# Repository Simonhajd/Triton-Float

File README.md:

# Triton Float

Development repository for the 2026 Triton Robotics Float.

## Overview

The Triton Float is being developed for the 2026 MATE ROV Pioneer competition (Newfoundland).
This design iteration is approximately 33% smaller than last year's model, while targeting more than 2× performance improvements in speed and significantly increased precision through layered redundancy and sensor feedback systems. It also includes a dedicated LoRa radio as opposed to last year's 4cm wire antenna, which will increase the reliability and robustness of the system.

## Features

Dimensions: 200mm x 4 in diameter.
Buoyancy system: PWM pump ranging from 220mL/min to -220mL/min.

Accuracy Strategy:

- Internal pressure sensor for ballast state verification  
- Pump movement feedback sensor for closed-loop control  
- Pre-calibrated pump flow rate modeling for predictive adjustment
- Additional onboard MCU sensors for reproducible control accuracy

## Hardware / Electrical

- Microcontroller: XIAO nRF52840 Sense  

- Sensors:  
  - XIAO nRF52840 Sense onboard IMU & sensors  
  - Blue Robotics Bar02  
  - Internal pressure sensor  
  - Pump movement sensor  

- Power System:  
  Custom voltage regulation system controlled via relay and magnetic hall-effect sensor on a secondary accessory PCB  

- PCB Revisions:  
  R2 completed, R3 in development

## Mechanical Design

Fusion / CAD link:
🔗 [View Fusion 360 CAD](https://a360.co/4slAPcB)

Notes:
### Structural Considerations:

Cylindrical housing designed to fit within a 4 in diameter constraint

Internal layout arranged to allow operation in the case of flooding (up to ~50-75% of internal volume) while maintaining core electronic functionality.

PCB mounted using tight-tolerance standoffs to prevent movement under vibration and ease serviceability

Layer system used to keep the float intact when the top flange and shell is removed.

### Integration Notes:

Limited internal volume required careful routing of wiring and tubing

Added solderable vias for power, in order to have a secure connection to the battery.

Accessory PCB used to isolate power regulation from main control logic

R3 revision addresses footprint issues and uses a different simpler power system for a working prototype.

## Current Status

- Version / Revision: R2
- In progress: R3, with fixed tracing and the internal pressure sensor.
- Completed: R2.
- Next steps: Testing R3 when it comes in.

## Tools 

- PCB software: KiCad
- CAD software: Fusion 360
- Firmware tools: C++

## Images

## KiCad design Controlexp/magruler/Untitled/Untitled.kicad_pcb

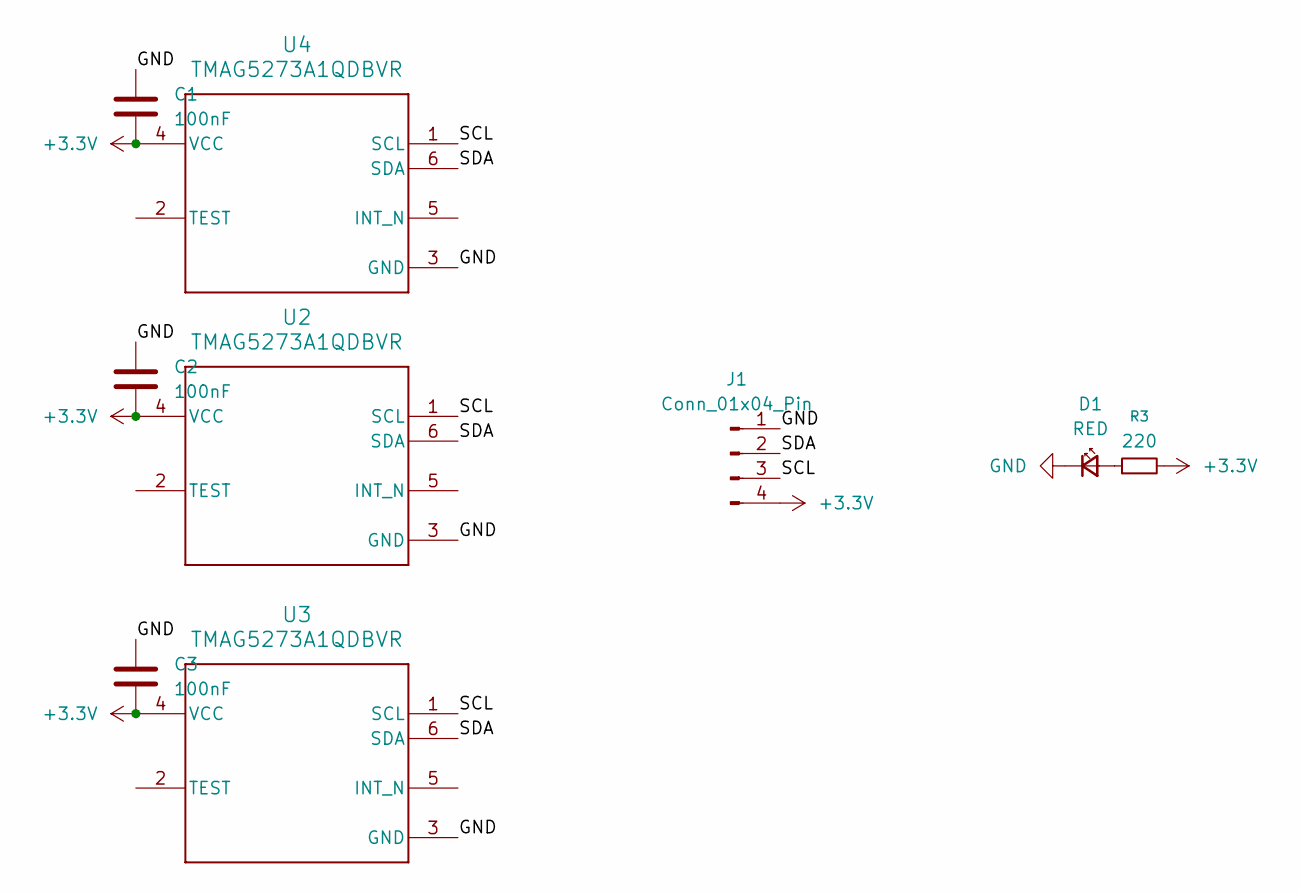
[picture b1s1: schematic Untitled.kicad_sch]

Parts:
C1, C2, C3: 100nF; C_0201_0603Metric
D1: RED; LED_0805_2012Metric
J1: Conn_01x04_Pin; JST_GH_BM04B-GHS-TBT_1x04-1MP_P1.25mm_Vertical
R3: 220; R_0603_1608Metric
U2, U3, U4: TMAG5273A1QDBVR; DBV0006A-IPC_A

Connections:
+3.3V: C1.2, C2.2, C3.2, J1.4, R3.2, U2.4 (VCC), U3.4 (VCC), U4.4 (VCC)
/SCL: J1.3, U2.1 (SCL), U3.1 (SCL), U4.1 (SCL)
/SDA: J1.2, U2.6 (SDA), U3.6 (SDA), U4.6 (SDA)
GND: C1.1, C2.1, C3.1, D1.1 (K), J1.1, U2.3 (GND), U3.3 (GND), U4.3 (GND)
unnamed: D1.2 (A), R3.1

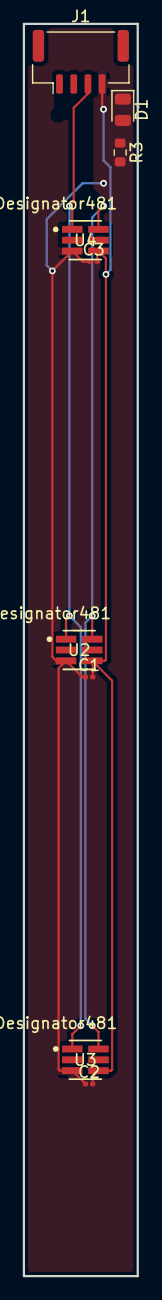
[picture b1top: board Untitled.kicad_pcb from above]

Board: 2 copper layers, 10.0 x 110.0 mm, 9 parts (0 on the bottom side), 5 nets.

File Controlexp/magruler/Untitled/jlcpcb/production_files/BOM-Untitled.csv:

Comment,Designator,Footprint,LCSC,Quantity
TMAG5273A1QDBVR,U2,DBV0006A-IPC_A,,1
100nF,C3,C_0201_0603Metric,,1
100nF,C2,C_0201_0603Metric,,1
Conn_01x04_Pin,J1,JST_GH_BM04B-GHS-TBT_1x04-1MP_P1.25mm_Vertical,,1
TMAG5273A1QDBVR,U4,DBV0006A-IPC_A,,1
TMAG5273A1QDBVR,U3,DBV0006A-IPC_A,,1
220,R3,R_0603_1608Metric,,1
RED,D1,LED_0805_2012Metric,,1
100nF,C1,C_0201_0603Metric,,1

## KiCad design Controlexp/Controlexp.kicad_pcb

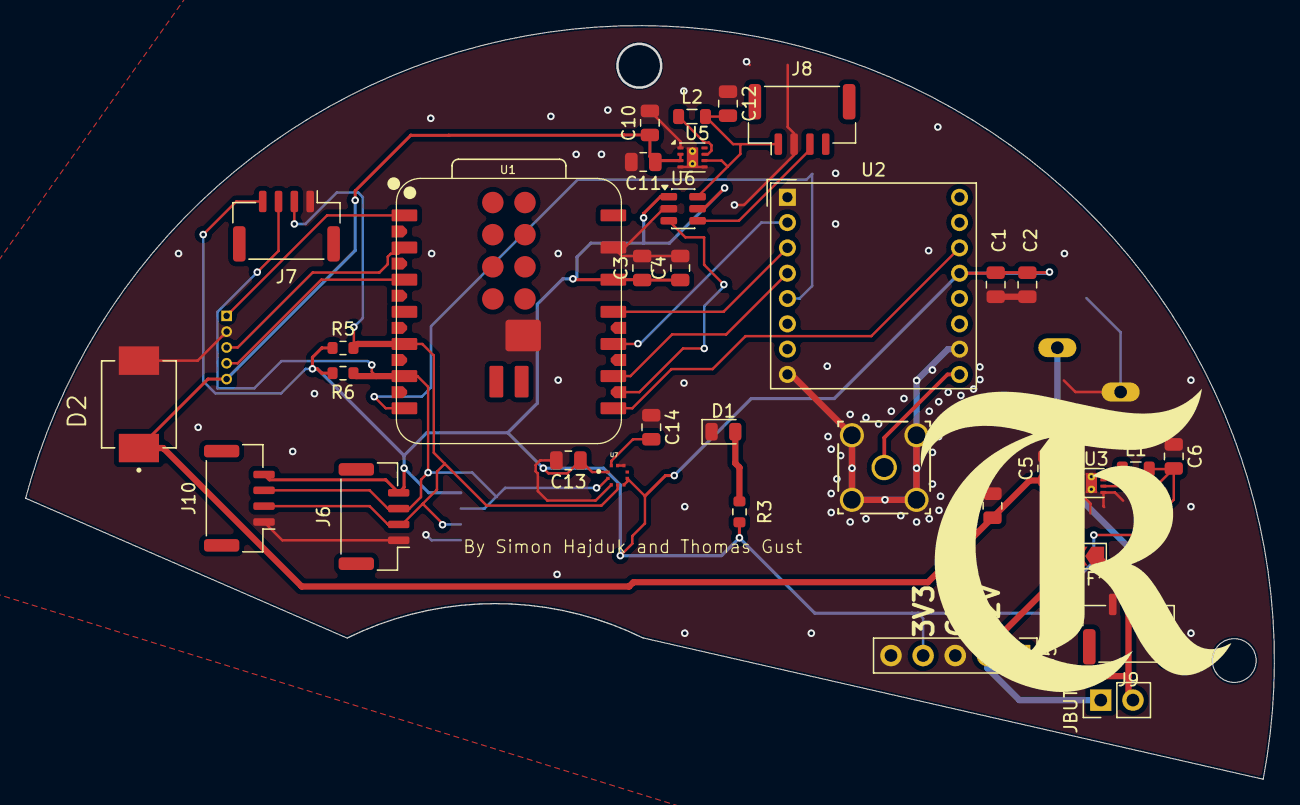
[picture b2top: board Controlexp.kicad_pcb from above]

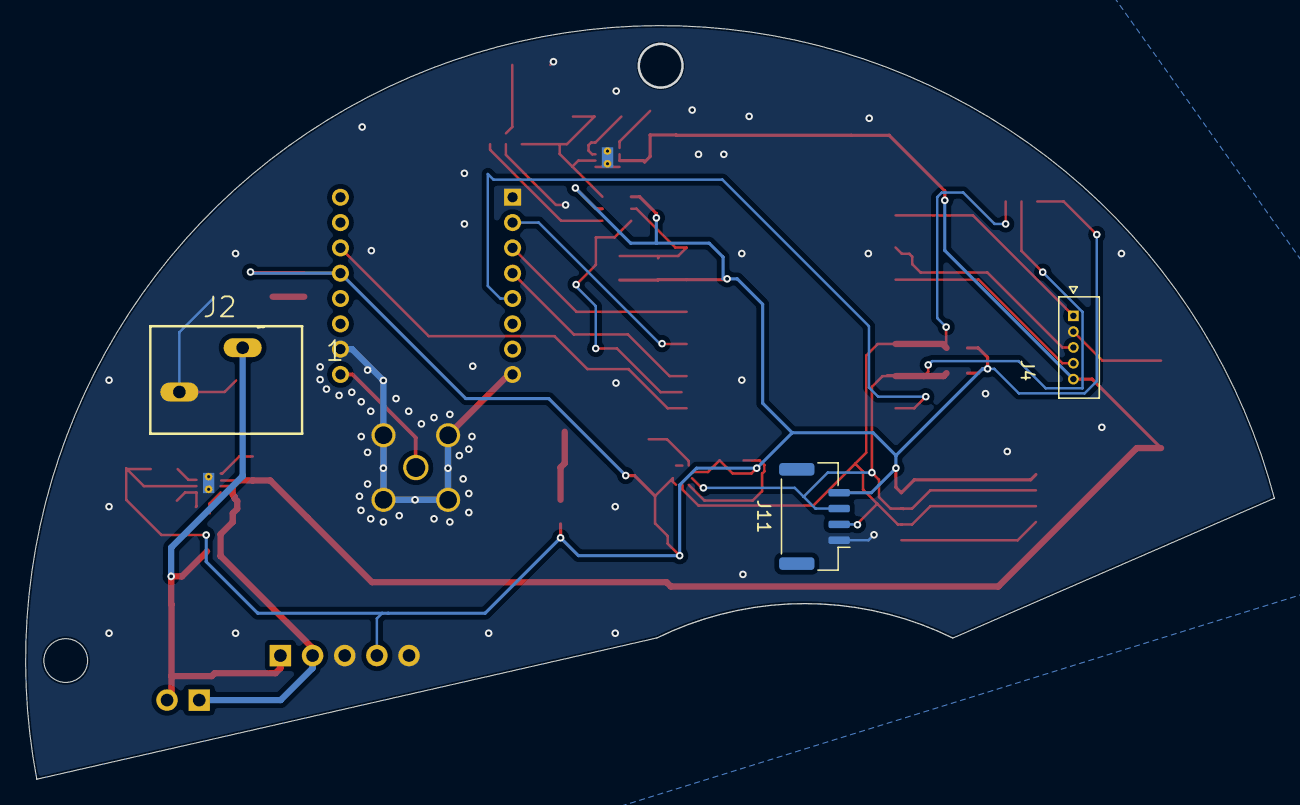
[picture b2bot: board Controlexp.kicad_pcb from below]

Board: 2 copper layers, 98.5 x 59.4 mm, 36 parts (3 on the bottom side), 21 nets.

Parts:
C1, C3: 0.1uF; C_0805_2012Metric
C2, C4: 10uF; C_0805_2012Metric
C5, C11: 10uF, 25V; C_0805_2012Metric
C6: 22uF, 6.3V; C_0805_2012Metric
C9, C10: 220 uF; C_0805_2012Metric
C12: 22uF, 10V; C_0805_2012Metric
C13, C14: 100nF; C_0805_2012Metric
D1: RED; LED_0805_2012Metric
D2: SS34; DIOM7959X265N
J1: Conn_Coaxial_Small; CONN_RF2-04A-T-00-50-G_ADM
J2: Conn_01x02; P-250-202
J4: 530470510; MOLEX_530470510
J5: Power Connector; PinHeader_1x05_P2.54mm_Vertical
J6: Pressure sensor; JST_GH_BM04B-GHS-TBT_1x04-1MP_P1.25mm_Vertical
J7: ToF sensor; JST_GH_BM04B-GHS-TBT_1x04-1MP_P1.25mm_Vertical
J8: LED; JST_GH_BM04B-GHS-TBT_1x04-1MP_P1.25mm_Vertical
J9: PWRCONN; JST_GH_BM03B-GHS-TBT_1x03-1MP_P1.25mm_Vertical
J10: Extra sensor TOP; JST_GH_BM04B-GHS-TBT_1x04-1MP_P1.25mm_Vertical
J11: Extra sensor BOTTOM; JST_GH_BM04B-GHS-TBT_1x04-1MP_P1.25mm_Vertical
JBUTT1: Conn_01x02; PinHeader_1x02_P2.54mm_Vertical
L1, L2: 2.2uH; L_0805_2012Metric
R3: 220; R_0603_1608Metric
R5, R6: 4.7k; R_0603_1608Metric
U1: XIAO-ESP32-S3-Plus-SMD
U2: RFM95W; HOPERF_RFM9XW_THT
U3: TPS62162DSG; WSON-8-1EP_2x2mm_P0.5mm_EP0.9x1.6mm_ThermalVias
U5: TPS62163DSG; WSON-8-1EP_2x2mm_P0.5mm_EP0.9x1.6mm_ThermalVias
U6: SN74LVC1T45DBV; SOT-23-6
U7: BMP388; XDCR_BMP388

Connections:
+3.3V: C1.1, C2.1, C3.1, C4.1, C6.2, C13.1, J5.4, J6.4, J7.4, J10.4, J11.4, L1.2, R3.2, R5.2, R6.2, U1.12 (3V3), U2.13 (3_3V), U3.6 (VOS), U6.1 (VCCA), U6.5 (DIR), U7.1 (VDDIO), U7.5 (SDO), U7.6 (CSB)
+5V: C12.2, J8.1, L2.2, U5.6 (VOS), U6.6 (VCCB)
+12V: C5.1, C9.1, C10.1, C11.1, D2.C, J2.L1 (Pin_1), J4.5, J5.1, J5.2, J9.2, JBUTT1.1, JBUTT1.2, U3.2 (VIN), U3.3 (EN), U5.2 (VIN), U5.3 (EN)
/ANT: J1.1 (In), U2.9 (ANT)
/BMPSCL: J6.3, J7.3, J10.3, J11.3, R6.1, U1.6 (GPIO6_A5_D5_SCL), U7.2 (SCK)
/BMPSDA: J6.2, J7.2, J10.2, J11.2, R5.1, U1.5 (GPIO5_A4_D4_SDA), U7.4 (SDI)
/DIN: J8.3, U6.4 (B)
/DIR: J4.3, U1.2 (GPIO2_A1_D1)
/FEEDBACK: J4.4, U1.3 (GPIO3_A2_D2)
/INT: U1.8 (GPIO44_D7_RX), U2.14 (DIO0)
/LEDSERIAL: U1.21 (GPIO11_DVP_Y8_SPI_MOSI1), U6.3 (A)
/MISO: U1.10 (GPIO8_A9_D9_MISO), U2.2 (MISO)
/MOSI: U1.11 (GPIO9_A10_D10_MOSI), U2.3 (MOSI)
/NSS: U1.7 (GPIO43_D6_TX), U2.5 (NSS)
/PWM: J4.1, U1.1 (GPIO1_A0_D0)
/SCK: U1.9 (GPIO7_A8_D8_SCK), U2.4 (SCK)
GND: C1.2, C2.2, C3.2, C4.2, C5.2, C6.1, C9.2, C10.2, C11.2, C12.1, C13.2, C14.1, D1.1 (K), D2.A, J1.2 (Ext), J1.3 (GND), J1.4 (GND), J1.5 (GND), J2.L2 (Pin_2), J4.2, J5.3, J5.5, J6.1, J7.1, J8.2, J9.1, J9.3, J10.1, J11.1, U1.13 (GND), U1.34 (PAD), U2.1 (GND), U2.8 (GND@1), U2.10 (GND@2), U3.1 (PGND), U3.4 (AGND), U3.5 (FB), U3.9 (PAD), U5.1 (PGND), U5.4 (AGND), U5.5 (FB), U5.9 (PAD), U6.2 (GND), U7.3 (VSS), U7.8 (VSS), U7.9 (VSS)
unnamed: D1.2 (A), R3.1
unnamed: L1.1, U3.7 (SW)
unnamed: L2.1, U5.7 (SW)
unnamed: C14.2, U7.10 (VDD)

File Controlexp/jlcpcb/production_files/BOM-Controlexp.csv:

Comment,Designator,Footprint,LCSC,Quantity
2.2uH,L2,L_0805_2012Metric,,1
SS34,D2,DIOM7959X265N,,1
Conn_01x02,J2,P-250-202,,1
0.1uF,C1,C_0805_2012Metric,,1
RED,D1,LED_0805_2012Metric,,1
2.2uH,L1,L_0805_2012Metric,,1
10uF,C2,C_0805_2012Metric,,1
530470510,J4,MOLEX_530470510,,1
RFM95W,,HOPERF_RFM9XW_THT,,0
Pressure sensor,J6,JST_GH_BM04B-GHS-TBT_1x04-1MP_P1.25mm_Vertical,,1
4.7k,R6,R_0603_1608Metric,,1
TPS62162DSG,U3,WSON-8-1EP_2x2mm_P0.5mm_EP0.9x1.6mm_ThermalVias,,1
10uF,C4,C_0805_2012Metric,,1
0.1uF,C3,C_0805_2012Metric,,1
Conn_Coaxial_Small,J1,CONN_RF2-04A-T-00-50-G_ADM,,1
"22uF, 6.3V",C6,C_0805_2012Metric,,1
"10uF, 25V",C5,C_0805_2012Metric,,1
4.7k,R5,R_0603_1608Metric,,1
TPS62163DSG,U5,WSON-8-1EP_2x2mm_P0.5mm_EP0.9x1.6mm_ThermalVias,,1
220,R3,R_0603_1608Metric,,1
220 uF,C9,C_0805_2012Metric,,1
Extra sensor TOP,J10,JST_GH_BM04B-GHS-TBT_1x04-1MP_P1.25mm_Vertical,,1
"10uF, 25V",C11,C_0805_2012Metric,,1
LED,J8,JST_GH_BM04B-GHS-TBT_1x04-1MP_P1.25mm_Vertical,,1
100nF,C14,C_0805_2012Metric,,1
Power Connector,J5,PinHeader_1x05_P2.54mm_Vertical,,1
Conn_01x02,JBUTT1,PinHeader_1x02_P2.54mm_Vertical,,1
220 uF,C10,C_0805_2012Metric,,1
ToF sensor,J7,JST_GH_BM04B-GHS-TBT_1x04-1MP_P1.25mm_Vertical,,1
100nF,C13,C_0805_2012Metric,,1
SN74LVC1T45DBV,U6,SOT-23-6,,1
BMP388,U7,XDCR_BMP388,,1
PWRCONN,J9,JST_GH_BM03B-GHS-TBT_1x03-1MP_P1.25mm_Vertical,,1
XIAO-ESP32-S3-Plus-SMD,U1,XIAO-ESP32-S3-Plus-SMD,,1
"22uF, 10V",C12,C_0805_2012Metric,,1
Extra sensor BOTTOM,J11,JST_GH_BM04B-GHS-TBT_1x04-1MP_P1.25mm_Vertical,,1

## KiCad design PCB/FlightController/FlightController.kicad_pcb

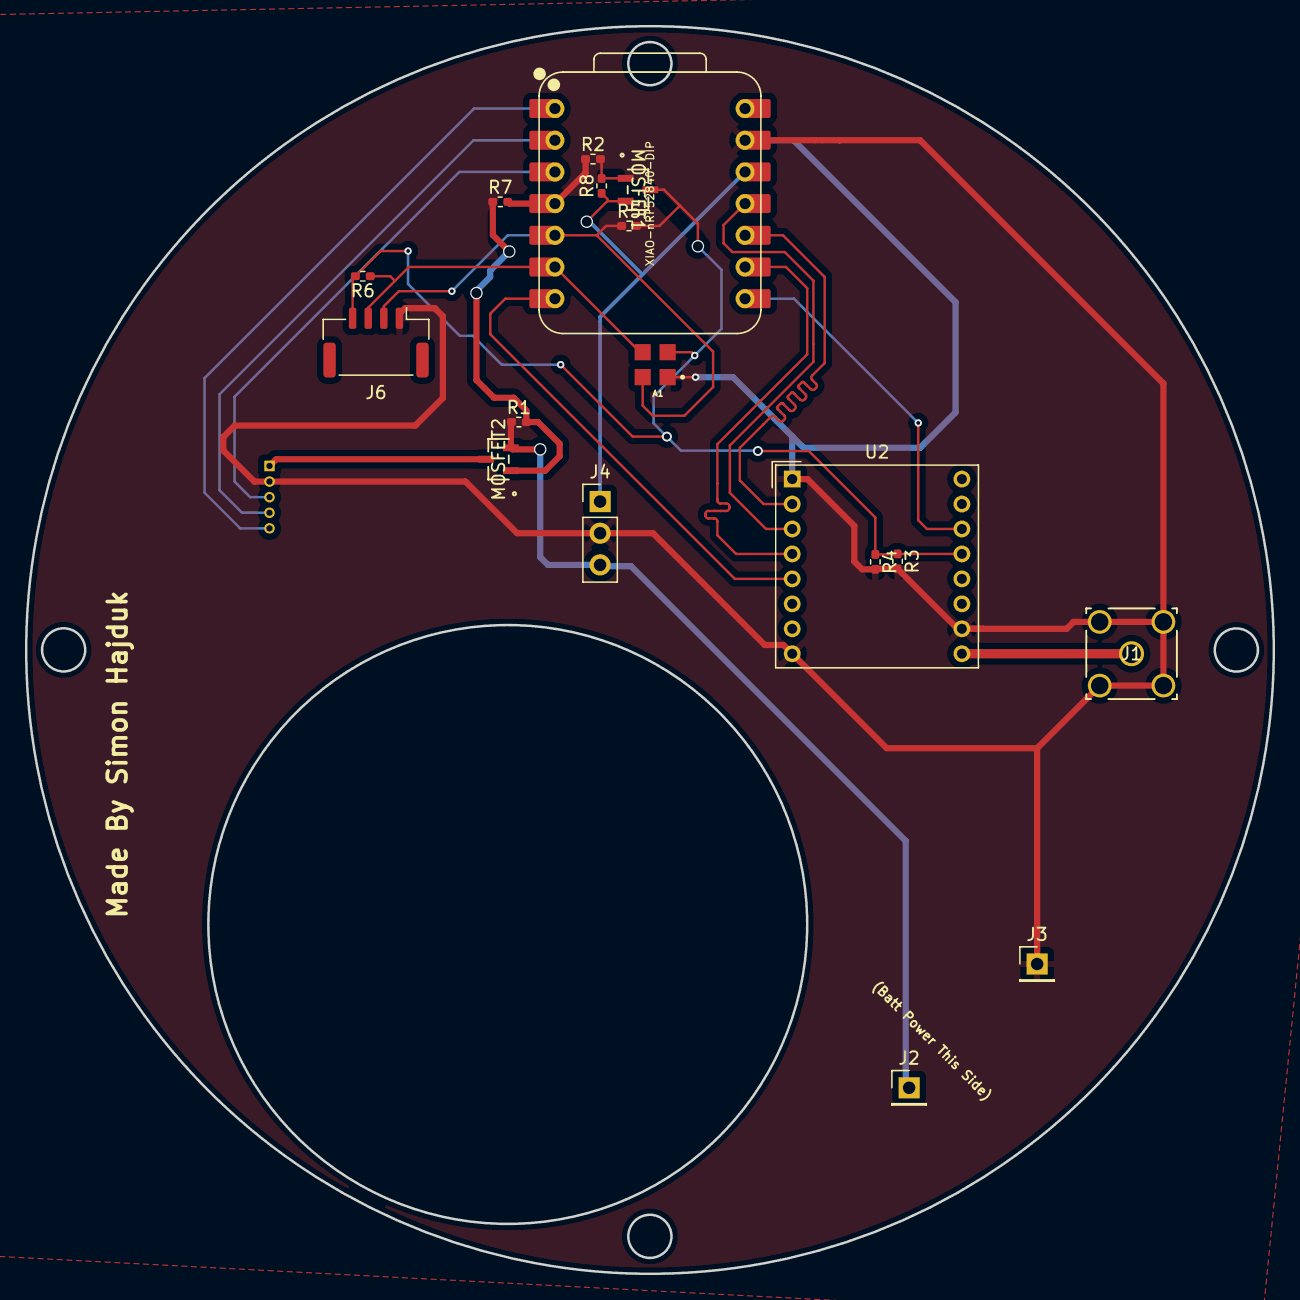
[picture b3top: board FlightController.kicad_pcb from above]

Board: 2 copper layers, 100.0 x 100.0 mm, 19 parts (1 on the bottom side), 17 nets.

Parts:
A1: MS583702BA01-50; XDCR_MS583702BA01-50
J1: SMA Connector; CONN_RF2-04A-T-00-50-G_ADM
J2: BATT IN; PinHeader_1x01_P2.54mm_Vertical
J3: BATT OUT; PinHeader_1x01_P2.54mm_Vertical
J4: BATT Reg IC; PinHeader_1x03_P2.54mm_Vertical
J6: Pressure sensor; JST_GH_BM04B-GHS-TBT_1x04-1MP_P1.25mm_Vertical
J8: 530470510; MOLEX_530470510
MOSFET1, MOSFET2: DMP3068L-7; SOT-23_DMP3068L_DIO
R1, R2, R5, R6, R7: 4.7k; R_0402_1005Metric_Pad0.72x0.64mm_HandSolder
R3: 0.1uF; R_0402_1005Metric_Pad0.72x0.64mm_HandSolder
R4: 10uF; R_0402_1005Metric_Pad0.72x0.64mm_HandSolder
R8: 10k; R_0402_1005Metric_Pad0.72x0.64mm_HandSolder
U1: XIAO-nRF52840-DIP
U2: RFM95W; HOPERF_RFM9XW_THT

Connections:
ANT: J1.1, U2.9 (ANT)
DIR: J8.4, U1.2 (PA4_A1_D1)
FEEDBACK: J8.5, U1.1 (PA02_A0_D0)
GND: A1.1 (GND), J3.1, J4.2 (GND), J6.1, J8.2, R3.2, R4.2, U1.13 (GND), U2.1 (GND), U2.8 (GND@1), U2.10 (GND@2)
INT: U1.8 (PB09_A7_D7_RX), U2.14 (DIO0)
MAIN: J2.1, J4.3 (VIN), MOSFET2.2 (S), R1.1
MISO: U1.10 (PA5_A9_D9_MISO), U2.2 (MISO)
MOSI: U1.11 (PA6_A10_D10_MOSI), U2.3 (MOSI)
NSS: U1.7 (PB08_A6_D6_TX), U2.5 (NSS)
PWM: J8.3, U1.3 (PA10_A2_D2)
PWRSwitch: MOSFET1.1 (G), MOSFET2.1 (G), R1.2, R2.1, R2.2, R7.1, R7.2, R8.2, U1.4 (PA11_A3_D3)
RAWSWPOWER: J8.1, MOSFET2.3 (D)
SCK: U1.9 (PA7_A8_D8_SCK), U2.4 (SCK)
SCL: A1.3 (SCL), J6.3, R6.1, U1.6 (PA9_A5_D5_SCL)
SDA: A1.4 (SDA), J6.2, R5.1, U1.5 (PA8_A4_D4_SDA)
SW3v3: A1.2 (VDD), J6.4, MOSFET1.3 (D), R3.1, R4.1, R5.2, R6.2, U2.13 (3_3V)
VOUT: J4.1 (VOUT), MOSFET1.2 (S), R8.1, U1.12 (3V3)

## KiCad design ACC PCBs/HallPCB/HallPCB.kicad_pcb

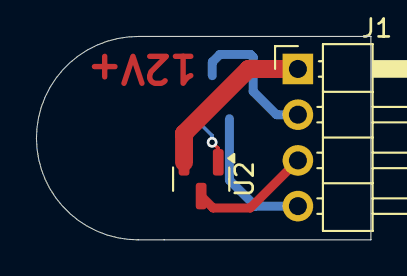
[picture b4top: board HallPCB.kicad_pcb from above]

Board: 2 copper layers, 18.6 x 11.3 mm, 3 parts (1 on the bottom side), 5 nets.

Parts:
HALL: TLE49643MXTMA1; PG-SOT23-3-15_INF
J1: Conn_01x04_Socket; PinHeader_1x04_P2.54mm_Horizontal
U2: AP2127N-1.0; SOT-23

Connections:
GND: HALL.3 (GND), J1.2
MAIN: J1.1, U2.2 (VO)
RAWSWPOWER: J1.3, U2.3 (VI)
SIG: HALL.2 (Q), U2.1 (GATE)
VOUT: HALL.1 (VDD), J1.4

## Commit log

2025-12-26 Made the PCB
2025-12-27 added a P-mosfet for the 3.3v wiring and let the 3.3v regulator "pre-power" the (now 4) pin switch system for the hall effect magnet sensor.
    added a P-mosfet for the 3.3v wiring and let the 3.3v regulator "pre-power" the (now 4) pin switch system for the hall effect magnet sensor.
2025-12-27 All boards should be finished. ACC otw, and an earlier version of the main board otw
2026-02-16 post R1 - flipped many traces and worked on adding an internal sensor for reduncancy
2026-02-16 Initial plan
2026-02-16 Initialize README.md with project details
    Added comprehensive details about the Triton Float project, including its overview, features, hardware specifications, mechanical design considerations, current status, tools used, and an optional im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
2026-02-16 add controlexp
2026-02-19 lil fixes + sma gnd fix.
    Added gnd stitching and connected the sma gnd. and fixed some connections
2026-03-08 Fix formatting of Images section in README
2026-03-08 Revise Tools section header in README
    Updated section headers for clarity and formatting.
2026-03-08 Update README with project details and status
2026-06-10 fresh board
